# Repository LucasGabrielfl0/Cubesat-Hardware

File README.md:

<h1 align="center"> ODYSSEY-HARDWARE</h1>

<p align="center">
  Repository for all the structural and electronic hardware for the ODYSSEY 2U CubeSat Prototype
</p>

## Main

## Battery

## EPS

## Frame and Structure for Reaction Wheels

## 🔗 Other Repositories in this Project
Here are the links for all the other repositores within this project
| Repository | Description |
|------------|-------------|
| [ODYSSEY-CubeSat](https://github.com/LucasGabrielfl0/Cubesat-ODYSSEY) | Embedded flight software for the CubeSat, from communications to the 3 axys attitude control system|
| [CubeSat-GroundStation](https://github.com/LucasGabrielfl0/Cubesat-GroundStation) | Embedded software responsible for communication with the satellite. |
| [CubeSat-Dashboard](https://github.com/LucasGabrielfl0/Cubesat-Dashboard) | Desktop interface for telemetry visualization and command transmission. |

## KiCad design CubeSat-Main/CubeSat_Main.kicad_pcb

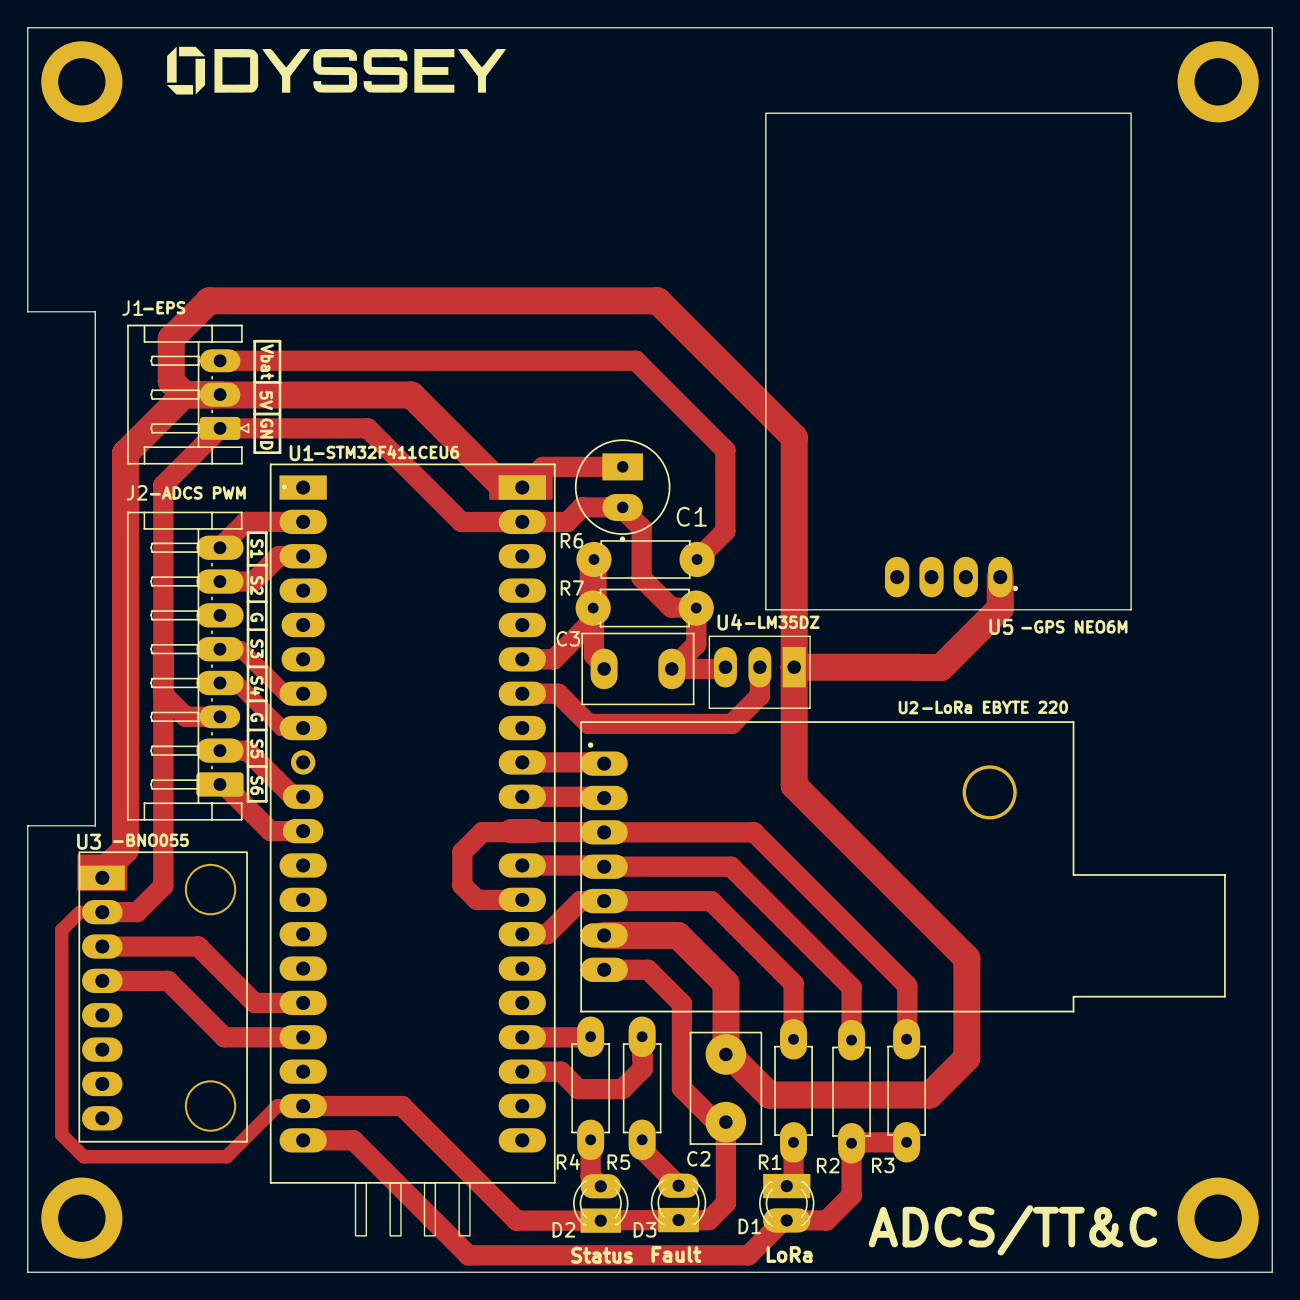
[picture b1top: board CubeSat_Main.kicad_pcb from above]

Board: 2 copper layers, 92.0 x 92.0 mm, 20 parts (0 on the bottom side), 24 nets.

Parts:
C1: 22uF; Cap_Electrolytic
C2, C3: 0.1uF; C_Disc_D8.0mm_W5.0mm_P5.00mm
D1, D3: LED; LED_D3.0mm
D2: LED_Faul; LED_D3.0mm
J1: Conn_01x03_Pin; JST_EH_S3B-EH_1x03_P2.50mm_Horizontal
J2: Conn_01x08_Socket; JST_EH_S8B-EH_1x08_P2.50mm_Horizontal
R1, R3, R7: 4.7K; R_Axial_DIN0207_L6.3mm_D2.5mm_P7.62mm_Horizontal
R2: 4.7k; R_Axial_DIN0207_L6.3mm_D2.5mm_P7.62mm_Horizontal
R4, R5: 1K; R_Axial_DIN0207_L6.3mm_D2.5mm_P7.62mm_Horizontal
R6: 10K; R_Axial_DIN0207_L6.3mm_D2.5mm_P7.62mm_Horizontal
U1: STM32F411CEU6 - BlackPill; STM32F411CEU_BlackPill
U2: LORA E220-900T22D; LORA-E220-900T22D
U3: BNO055
U4: LM35-LP; LM35DZ
U5: GPS_NEO6M

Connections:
BNO055_SCL: U1.45 (PB8), U3.3 (SCL\RX)
BNO055_SDA: U1.46 (PB9), U3.4 (SDA\TX)
E220_AUX: R1.1, U1.11 (PA1), U2.5 (AUX)
E220_M0: U1.16 (PA6), U2.1 (MO)
E220_M1: U1.15 (PA5), U2.2 (M1)
E220_RX: R3.1, U1.12 (PA2), U1.14 (PA4), U2.3 (RXD)
E220_TX: R2.1, U1.13 (PA3), U2.4 (TXD)
GND: C1.2, C2.1, C3.1, D2.1 (K), D3.1 (K), J1.1, J2.3, R7.2, U1.23 (GND), U1.47 (GND), U2.7 (GND), U3.2 (GND), U4.3 (GND)
LED_BLUE: R4.1, U1.4 (PC15)
LED_RED: R5.1, U1.3 (PC14)
M1_PWM1: J2.8, U1.26 (PB13)
M1_PWM2: J2.7, U1.27 (PB14)
M2_PWM1: J2.5, U1.31 (PA10)
M2_PWM2: J2.4, U1.32 (PA11)
M3_PWM1: J2.2, U1.38 (PA15)
M3_PWM2: J2.1, U1.39 (PB3)
unnamed: D1.1 (K), R1.2
unnamed: D2.2 (A), R4.2
unnamed: D3.2 (A), R5.2
STM_3.3V: D1.2 (A), R2.2, R3.2, U1.48 (3V3)
Temp_ADC: U1.18 (PB0), U4.2 (V_{OUT})
VIN_5V: C1.1, C2.2, J1.2, U1.5V, U2.6 (VCC), U3.1 (VIN), U4.1 (+V_{S}), U5.1 (VCC)
Vbat_8.4V: J1.3, R6.1
Vbat_ADC: C3.2, R6.2, R7.1, U1.19 (PB1)

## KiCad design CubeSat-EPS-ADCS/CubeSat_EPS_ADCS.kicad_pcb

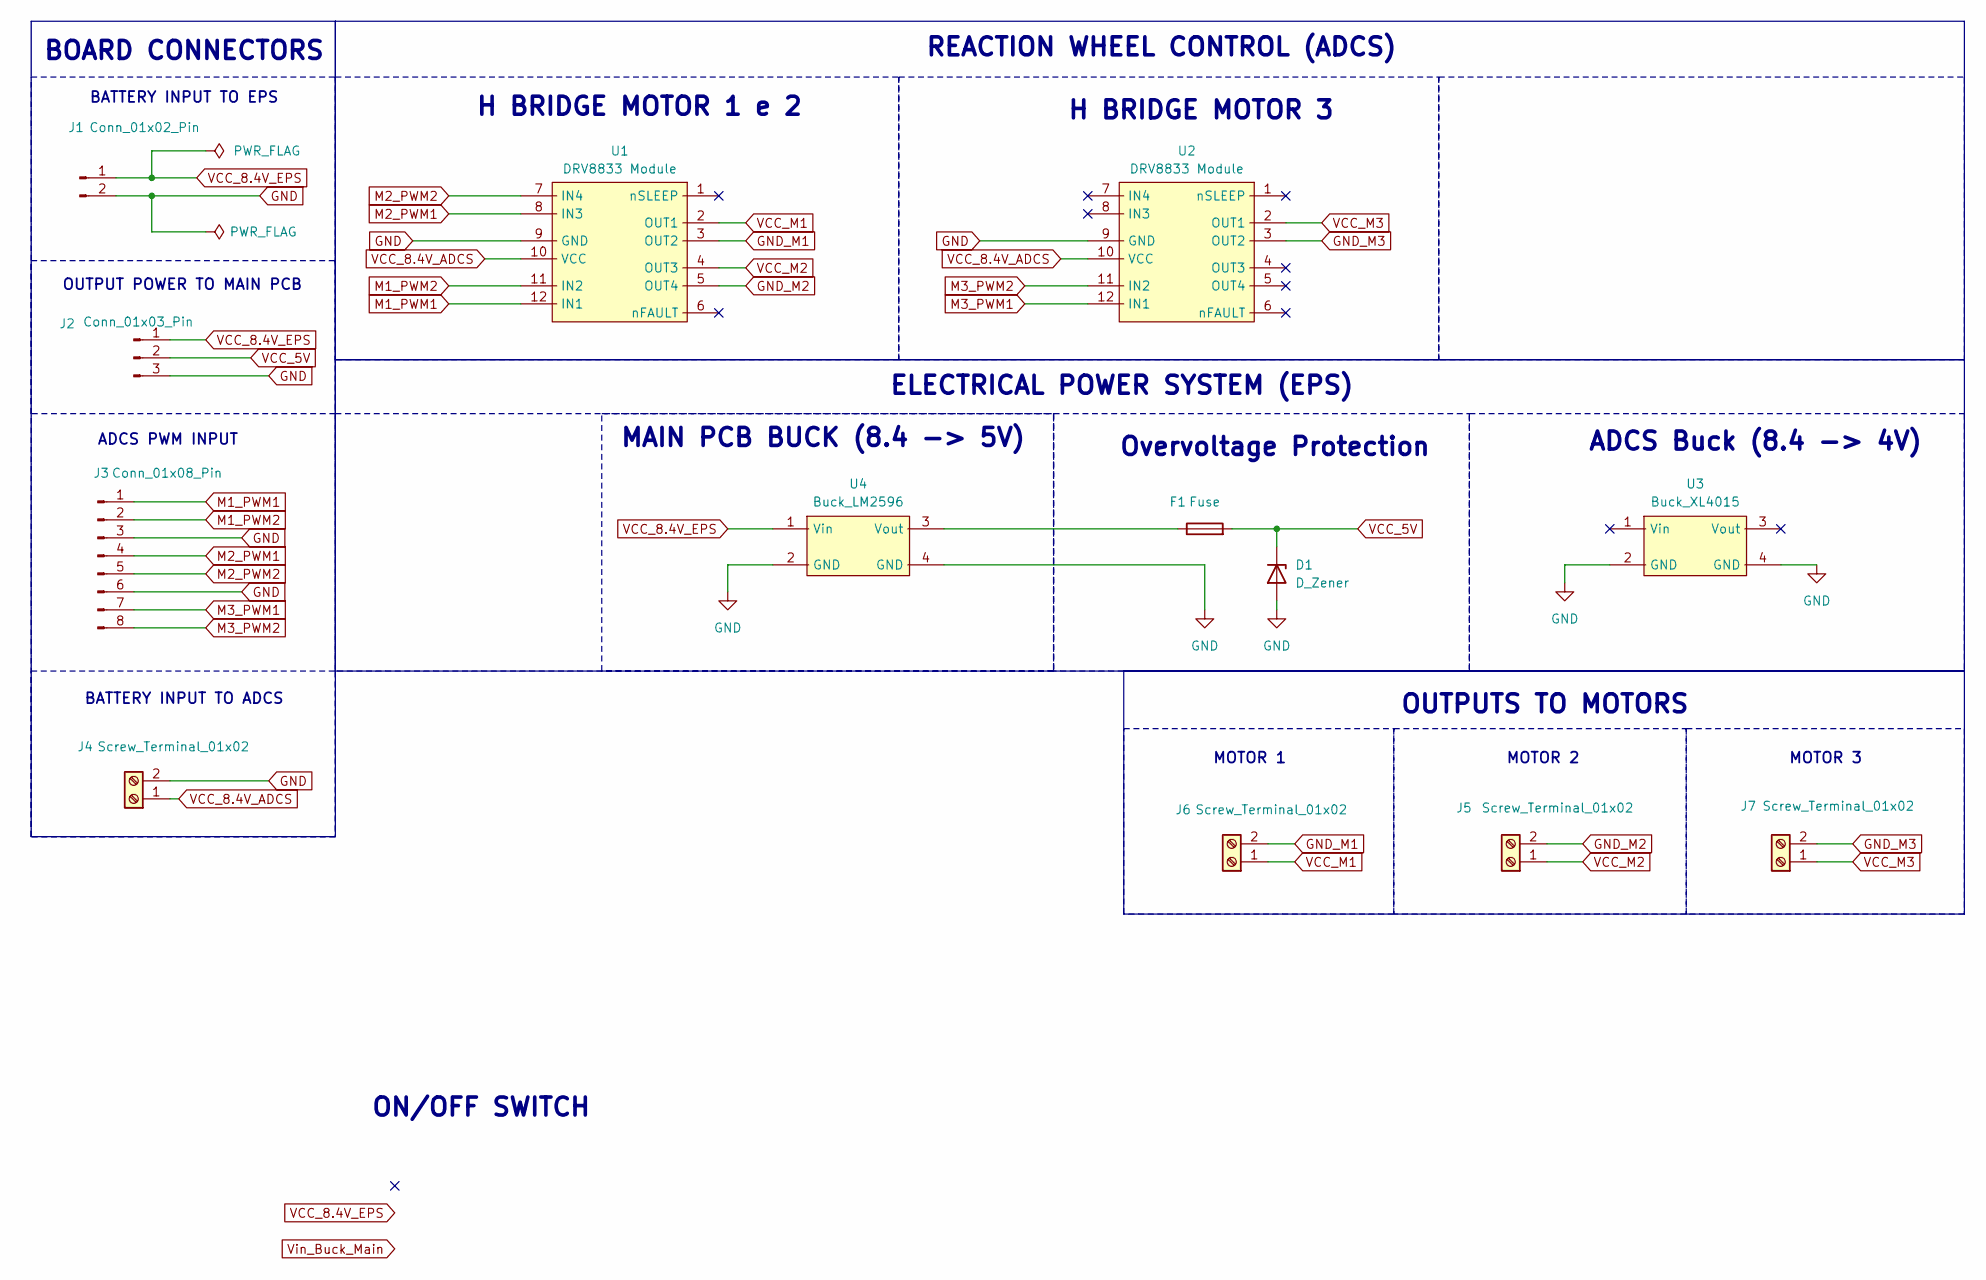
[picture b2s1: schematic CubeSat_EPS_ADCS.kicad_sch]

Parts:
D1: D_Zener; D_5W_P10.16mm_Horizontal
F1: Fuse; FUSE_4527
J1: Conn_01x02_Pin; JST_EH_B2B-EH-A_1x02_P2.50mm_Vertical
J2: Conn_01x03_Pin; JST_EH_B3B-EH-A_1x03_P2.50mm_Vertical
J3: Conn_01x08_Pin; JST_EH_B8B-EH-A_1x08_P2.50mm_Vertical
J4, J5, J6: Screw_Terminal_01x02; TerminalBlock_Phoenix_MKDS-1,5-2_1x02_P5.00mm_Horizontal
J7: Screw_Terminal_01x02; TerminalBlock_Phoenix_MKDS-1,5-2-5.08_1x02_P5.08mm_Horizont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
U1, U2: DRV8833 Module; DRV8833
U3: Buck_XL4015
U4: Buck_LM2596

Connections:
GND: D1.2 (A), J1.2, J2.3, J3.3, J3.6, J4.2, U1.9 (GND), U2.9 (GND), U3.2 (GND), U3.4 (GND), U4.2 (GND), U4.4 (GND)
GND_M1: J6.2, U1.3 (OUT2)
GND_M2: J5.2, U1.5 (OUT4)
GND_M3: J7.2, U2.3 (OUT2)
M1_PWM1: J3.1, U1.12 (IN1)
M1_PWM2: J3.2, U1.11 (IN2)
M2_PWM1: J3.4, U1.8 (IN3)
M2_PWM2: J3.5, U1.7 (IN4)
M3_PWM1: J3.7, U2.12 (IN1)
M3_PWM2: J3.8, U2.11 (IN2)
unnamed: F1.1, U4.3 (Vout)
VCC_5V: D1.1 (K), F1.2, J2.2
VCC_8.4V_ADCS: J4.1, U1.10 (VCC), U2.10 (VCC)
VCC_8.4V_EPS: J1.1, J2.1, U4.1 (Vin)
VCC_M1: J6.1, U1.2 (OUT1)
VCC_M2: J5.1, U1.4 (OUT3)
VCC_M3: J7.1, U2.2 (OUT1)

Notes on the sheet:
H BRIDGE MOTOR 1 e 2
BATTERY INPUT TO ADCS
REACTION WHEEL CONTROL (ADCS)
OUTPUT POWER TO MAIN PCB
ELECTRICAL POWER SYSTEM (EPS)
BATTERY INPUT TO EPS
OUTPUTS TO MOTORS
MAIN PCB BUCK (8.4 -> 5V)
ADCS PWM INPUT
Overvoltage Protection
BOARD CONNECTORS
ADCS Buck (8.4 -> 4V)
H BRIDGE MOTOR 3
MOTOR 2
ON/OFF SWITCH
MOTOR 3
MOTOR 1

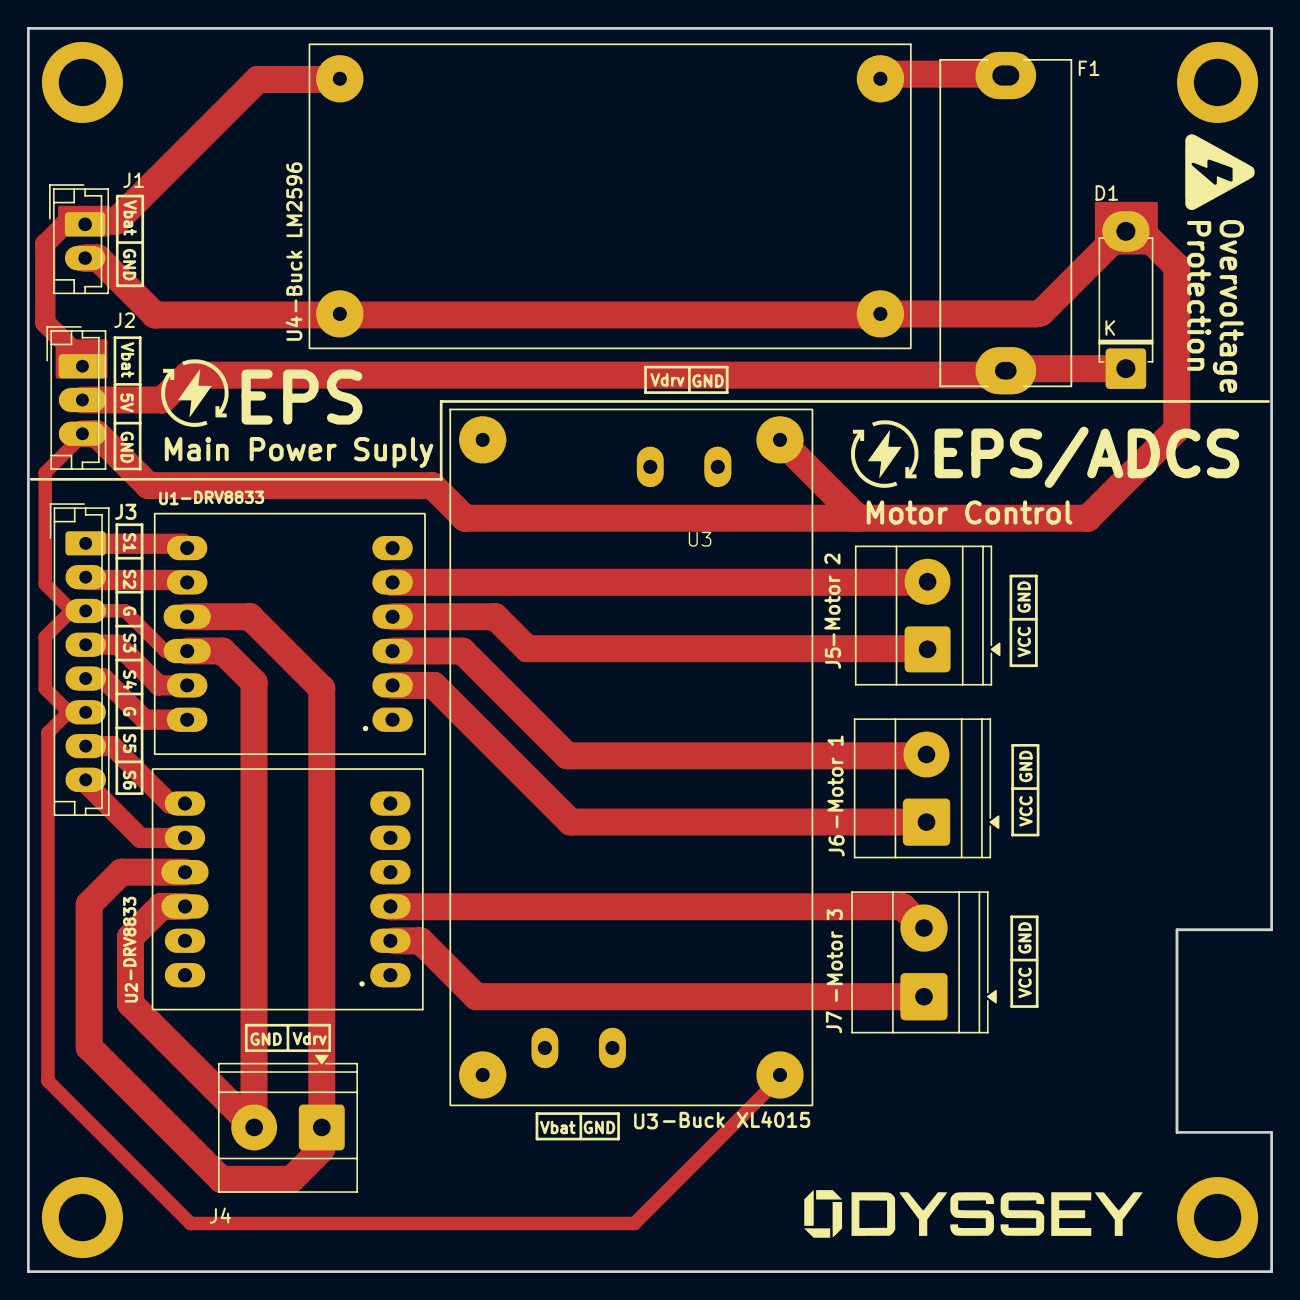
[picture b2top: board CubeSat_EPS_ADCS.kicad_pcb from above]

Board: 2 copper layers, 92.0 x 92.0 mm, 13 parts (0 on the bottom side), 17 nets.

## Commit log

2026-04-24 First complete version of all the PCBs
2026-04-29 Mostly fine tuning the boards, also added capacitor for battery ADC
2026-05-12 Changing the size of all traces to fit the 1 mm requirement of the draft PCB
2026-05-14 final version of the 3 PCBs, minor size changes for the protoypes
2026-05-14 final changes
2026-05-14 new files
2026-05-14 version with the right hole setup
2026-05-14 new files2
2026-05-18 add new drill format
2026-05-19 new origin placement
2026-05-19 new origin placement + update all
2026-05-23 final changes in ALL 3 pcbs: mounting wholes config, and a few connector changes
2026-05-25 last minute changes, adding kill swithc and backup buck converter for the motors
2026-05-26 Add all most recent changes: EPS switch/extra buck update / Battery connector update
2026-05-26 changing the size of the vias
2026-05-26 Battery PCB connector update
2026-05-26 small changes
2026-05-26 safety size change
2026-06-01 new Main and EPS PCBs, all previous problems corrected, final version
2026-06-01 adding the unused pin as smd, instead of just removing it
2026-06-02 change in the GPS location, so it doesnt smash into its antenna
2026-06-02 small changes only
2026-06-02 small changes in layout
2026-06-07 FIrst real update of the readme, just the backbone
2026-06-08 Adding Pictures to readme
2026-06-08 minor changes in the design
